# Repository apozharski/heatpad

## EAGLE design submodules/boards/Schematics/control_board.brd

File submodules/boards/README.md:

View this project on [CADLAB.io](https://cadlab.io/project/23046). 

# heat-control-pcb
Physical hardware for the Heat/Humidity/general-purpose ecostat.

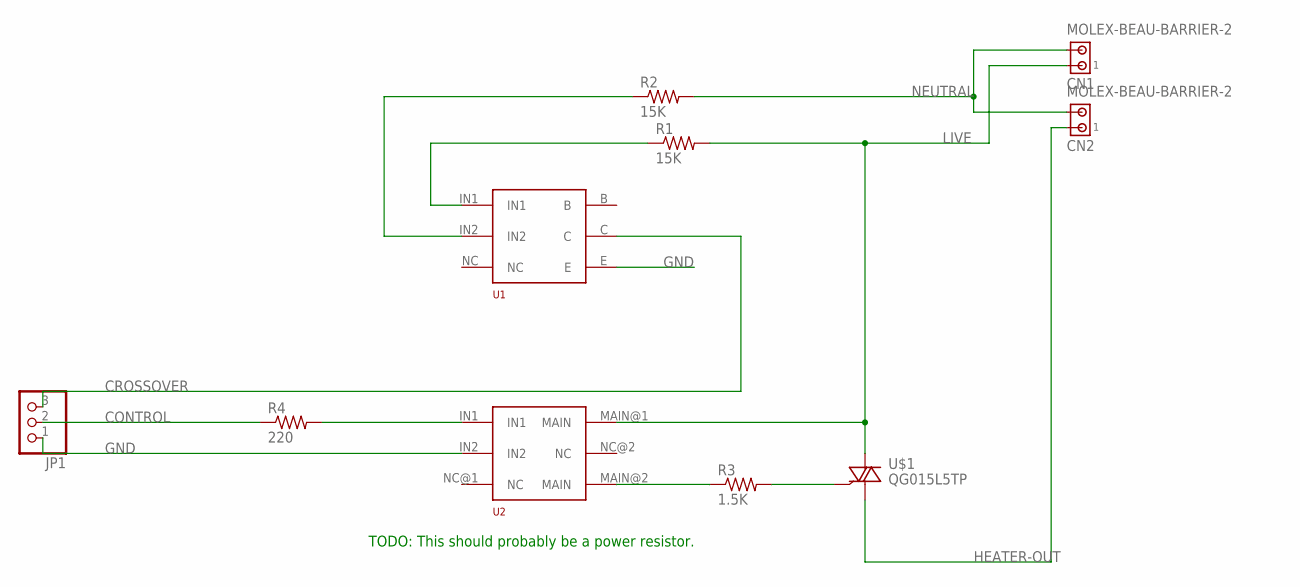
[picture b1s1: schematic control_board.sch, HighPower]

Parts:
CN1, CN2: MOLEX-BEAU-BARRIER-2
JP1: PINHD-1X3/90; 1X03/90
R1, R2: 15K; RSF100
R3: 1.5K; CR-25
R4: 220; CR-25
U1: H11AA4M
U2: MOC3052M
U$1: QG015L5TP

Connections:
CONTROL: JP1.2, R4.P$1 (1)
CROSSOVER: JP1.3, U1.C
GND: JP1.1, U1.E, U2.IN2
HEATER-OUT: CN2.P1 (1), U$1.P$1 (A1)
LIVE: CN1.P1 (1), R1.P$2 (2), U2.MAIN@1 (MAIN), U$1.P$3 (A2)
unnamed: R2.P$1 (1), U1.IN2
unnamed: R1.P$1 (1), U1.IN1
unnamed: R3.P$1 (1), U2.MAIN@2 (MAIN)
unnamed: R3.P$2 (2), U$1.P$2 (G)
unnamed: R4.P$2 (2), U2.IN1
NEUTRAL: CN1.P2 (2), CN2.P2 (2), R2.P$2 (2)

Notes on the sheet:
TODO: This should probably be a power resistor.

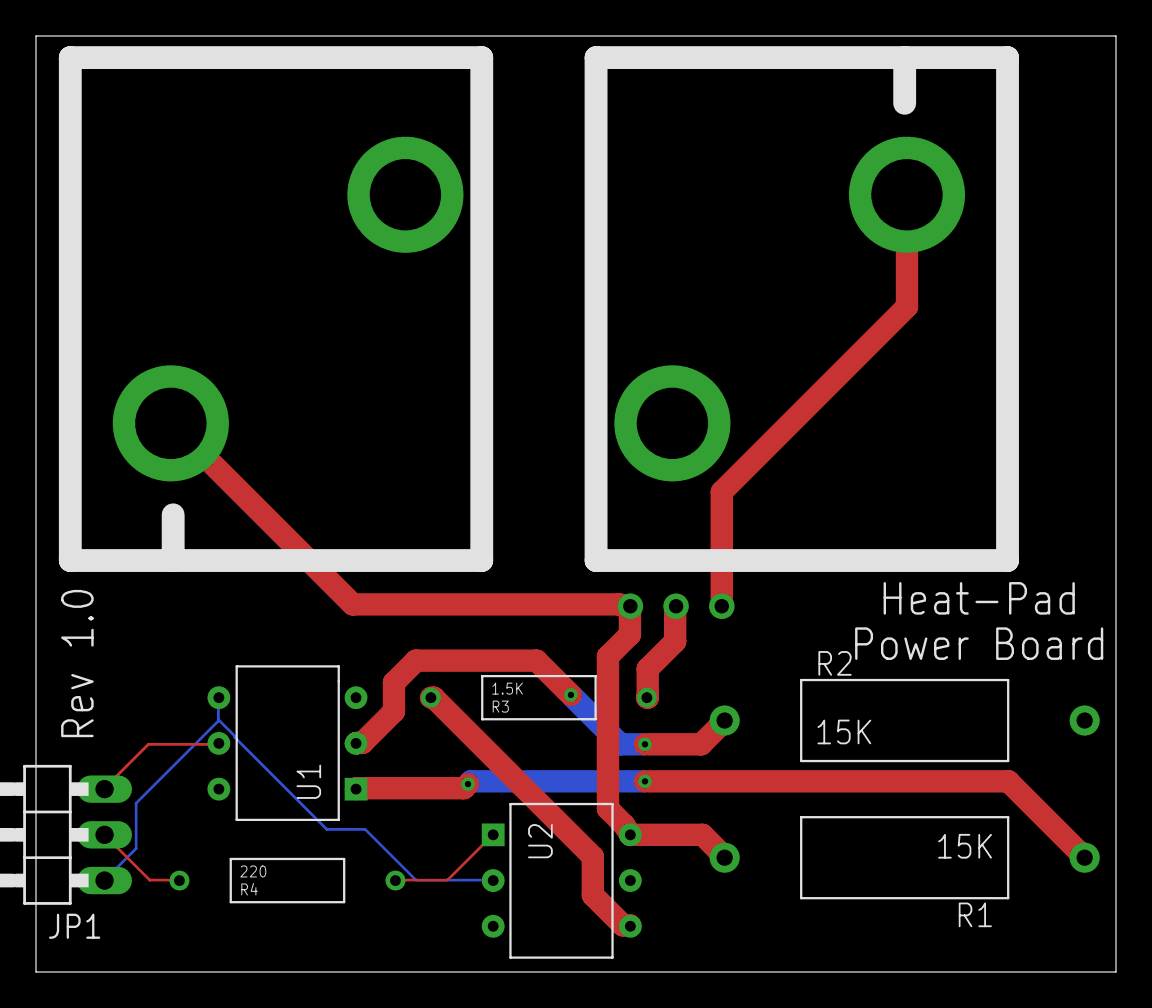
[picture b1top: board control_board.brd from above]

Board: 2 copper layers, 60.0 x 52.0 mm, 10 parts (0 on the bottom side), 11 nets.

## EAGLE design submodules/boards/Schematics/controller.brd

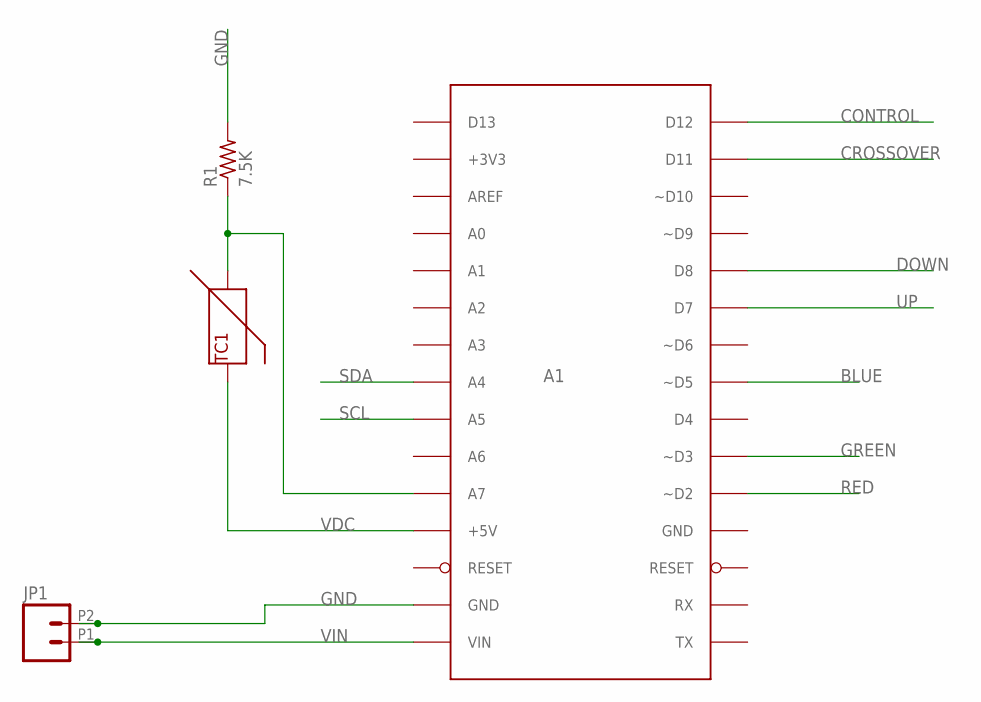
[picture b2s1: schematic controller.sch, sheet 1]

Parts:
A1: NANO_EVERY; NANO_EVERY_SOCKET
JP1: 1716060000; WM2-2
R1: 7.5K; CFR-25
TC1: MA100GG103AN

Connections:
BLUE: A1.~D5; also elsewhere on the board
CONTROL: A1.D12; also elsewhere on the board
CROSSOVER: A1.D11; also elsewhere on the board
DOWN: A1.D8; also elsewhere on the board
GND: A1.GND@1 (GND), JP1.P2 (2), R1.P$2 (2); also elsewhere on the board
GREEN: A1.~D3; also elsewhere on the board
unnamed: A1.A7, R1.P$1 (1), TC1.P$2
RED: A1.~D2; also elsewhere on the board
SCL: A1.A5; also elsewhere on the board
SDA: A1.A4; also elsewhere on the board
UP: A1.D7; also elsewhere on the board
VDC: A1.+5V, TC1.P$1; also elsewhere on the board
VIN: A1.VIN, JP1.P1 (1)

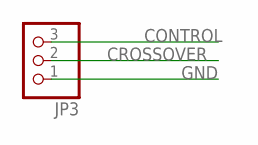
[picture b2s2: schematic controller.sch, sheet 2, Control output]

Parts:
JP3: PINHD-1X3/90; 1X03/90

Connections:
CONTROL: JP3.3; also elsewhere on the board
CROSSOVER: JP3.2; also elsewhere on the board
GND: JP3.1; also elsewhere on the board

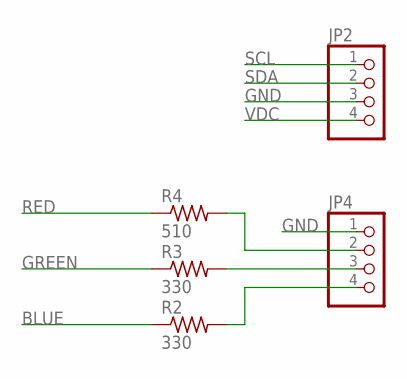
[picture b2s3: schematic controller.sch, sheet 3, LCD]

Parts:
JP2, JP4: PINHD-1X4; 1X04
R2, R3: 330; CFR-25
R4: 510; CFR-25

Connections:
BLUE: R2.P$1 (1); also elsewhere on the board
GND: JP2.3, JP4.1; also elsewhere on the board
GREEN: R3.P$1 (1); also elsewhere on the board
unnamed: JP4.4, R2.P$2 (2)
unnamed: JP4.3, R3.P$2 (2)
unnamed: JP4.2, R4.P$2 (2)
RED: R4.P$1 (1); also elsewhere on the board
SCL: JP2.1; also elsewhere on the board
SDA: JP2.2; also elsewhere on the board
VDC: JP2.4; also elsewhere on the board

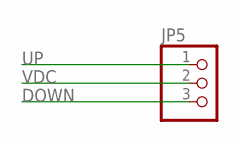
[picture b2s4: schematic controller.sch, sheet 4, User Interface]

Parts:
JP5: PINHD-1X3; 1X03

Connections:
DOWN: JP5.3; also elsewhere on the board
UP: JP5.1; also elsewhere on the board
VDC: JP5.2; also elsewhere on the board

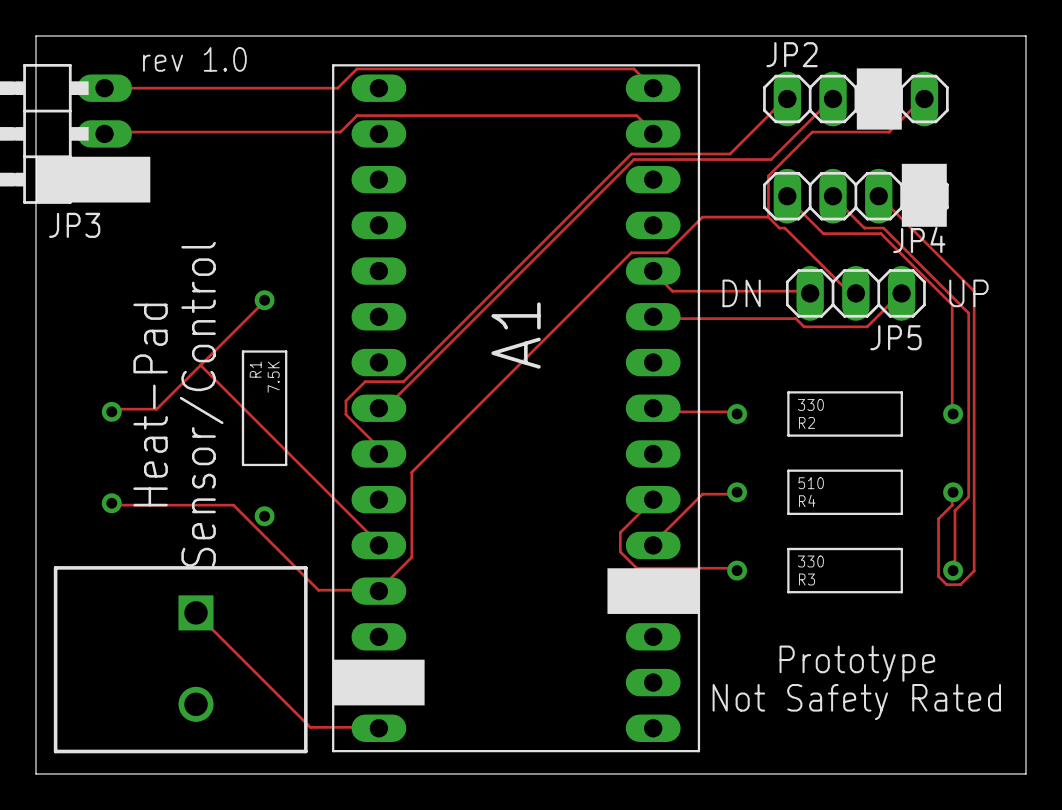
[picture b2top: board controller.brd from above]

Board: 2 copper layers, 55.0 x 41.0 mm, 11 parts (0 on the bottom side), 16 nets.

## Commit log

2020-04-01 heatpad
2020-04-01 Cleanup structure
2020-07-19 removing basic ino, adding submodule
2020-07-19 Add basic sketch
2020-08-01 initial tests
2020-08-05 Correct zero crossing code
2020-08-12 Working/tuned but with some jitter.
